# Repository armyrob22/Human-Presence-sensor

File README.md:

# Human-Presence-sensor

This is my second version of this board. My first board had many errors and was basically unusable. The pin headers were not aligned once i got the boards. This made it impossible to use the esp32 dev board I had. The biggest failure was the fact that i misplaced the USB type C connector. It was not close enough to the edge for me to plug in a power cable. This design puts the ESP32 on the PCB and lets just the mmWave 24Ghz radar board plug into a pin header. This design forced me to learn how to really design a buck converter circuit so i can take the 5V USB input power and drop it down to 3.3V required for the MCU. I took it a step further and I really drilled down on learning the physic's and the equations to derive what you need for a buck converter.

This is the result of my python script running a simulation of my chosen buck converter. I ran several different versions to see if my inductor sizing was correct. The reference design I used for most of my layout turned out to be really good for my given circuit. This is why i chose a 4.7uH inductor for my design. Even though this is my project and my own board I tried to treat it with the same care I will bring to the work place when I get to design other boards. The next big piece of the buck converter was to figure out the feedback sense resistor values required. My converter has a reference voltage of 0.8v. This means the formula I used is
Vout = Vref × (1 + R1/R2)
Vref = 0.8V, R2 = 12.7k, R1 = 40.2k
Vout = 0.8 × (1 + 40.2/12.7) = 3.33V

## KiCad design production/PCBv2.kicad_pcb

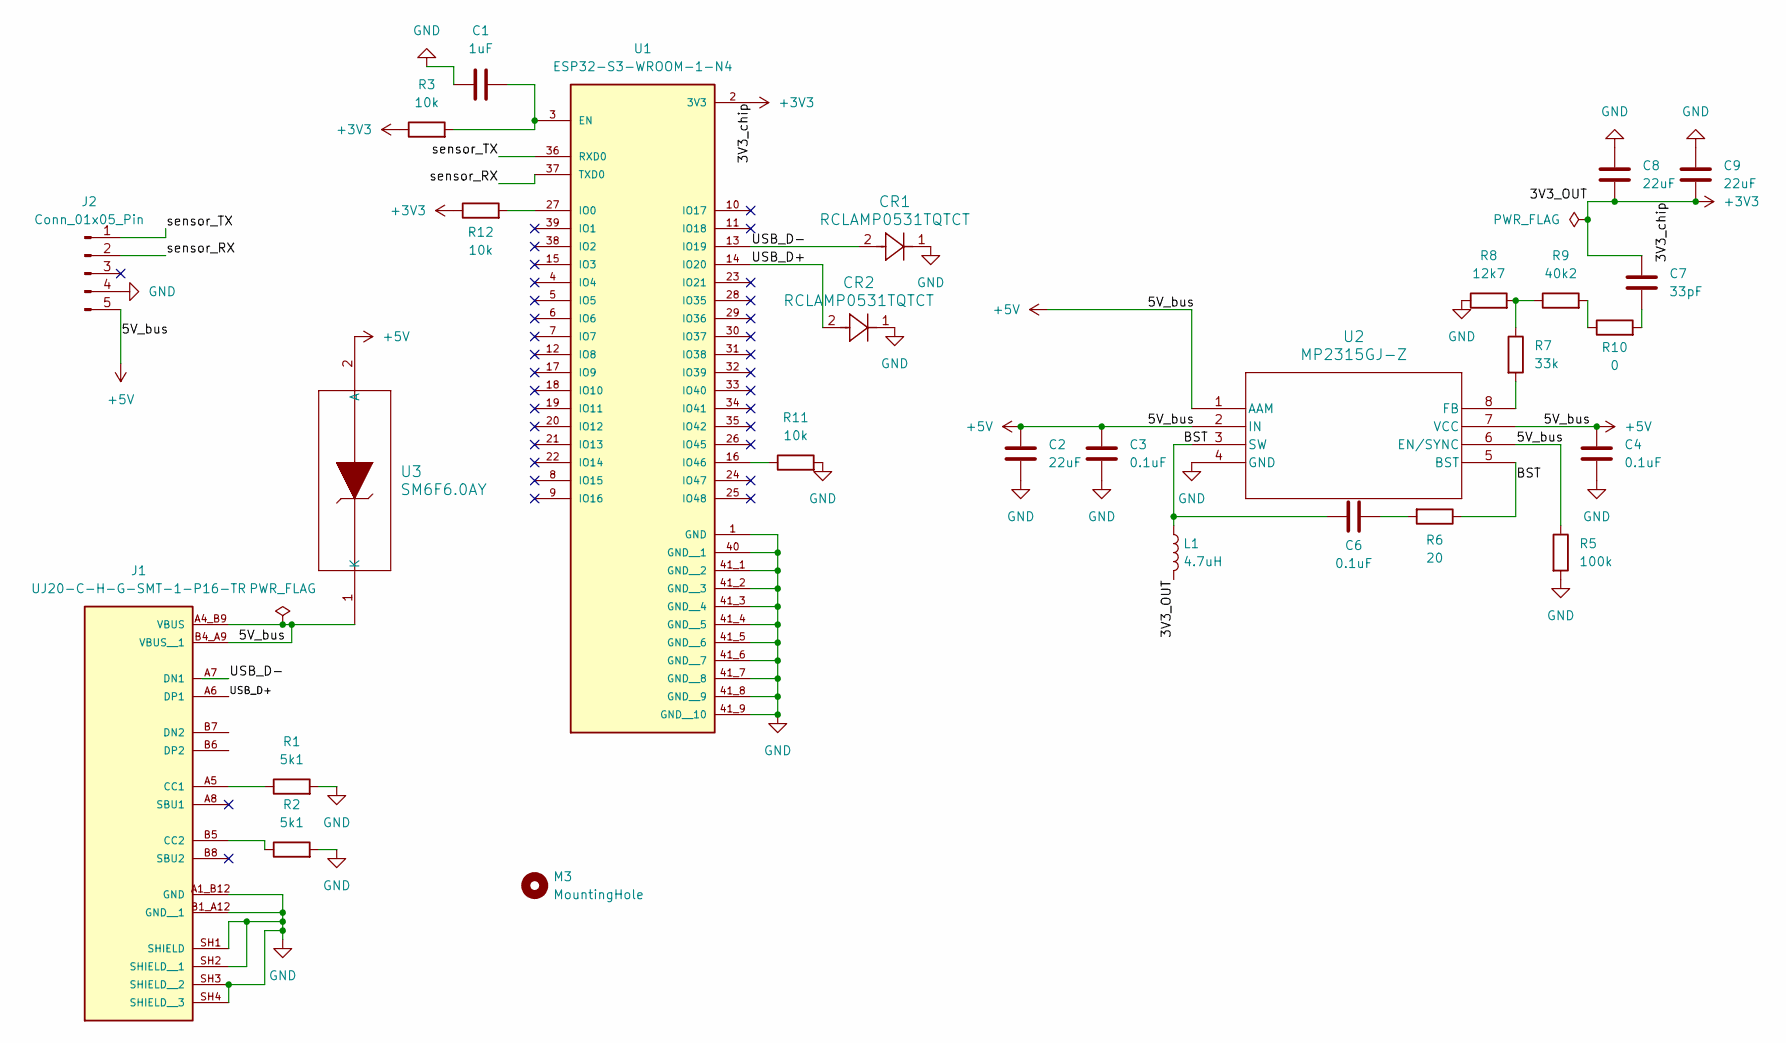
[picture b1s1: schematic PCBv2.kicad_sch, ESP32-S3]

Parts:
C1: 1uF; C_0805_2012Metric_Pad1.18x1.45mm_HandSolder
C2, C8, C9: 22uF; C_0805_2012Metric_Pad1.18x1.45mm_HandSolder
C3, C4, C6: 0.1uF; C_0805_2012Metric_Pad1.18x1.45mm_HandSolder
C7: 33pF; C_0805_2012Metric_Pad1.18x1.45mm_HandSolder
CR1, CR2: RCLAMP0531TQTCT; CR_RCLAMP053_1XP6_SEM-L
J1: UJ20-C-H-G-SMT-1-P16-TR; SAMESKY_UJ20-C-H-G-SMT-1-P16-TR; PARTREV 1.0
J2: Conn_01x05_Pin; PinHeader_1x05_P2.54mm_Vertical
L1: 4.7uH; IND_DFE322520FD-4R7M=P2_MUR
M3: MountingHole; MountingHole_3.2mm_M3_DIN965_Pad
R1, R2: 5k1; R_0805_2012Metric_Pad1.20x1.40mm_HandSolder
R3, R11, R12: 10k; R_0805_2012Metric_Pad1.20x1.40mm_HandSolder
R5: 100k; R_0805_2012Metric_Pad1.20x1.40mm_HandSolder
R6: 20; R_0805_2012Metric_Pad1.20x1.40mm_HandSolder
R7: 33k; R_0805_2012Metric_Pad1.20x1.40mm_HandSolder
R8: 12k7; R_0805_2012Metric_Pad1.20x1.40mm_HandSolder
R9: 40k2; R_0805_2012Metric_Pad1.20x1.40mm_HandSolder
R10: 0; R_0805_2012Metric_Pad1.20x1.40mm_HandSolder
U1: ESP32-S3-WROOM-1-N4; XCVR_ESP32-S3-WROOM-1-N4; PARTREV v1.0
U2: MP2315GJ-Z; TSOT23-8_MPS
U3: SM6F6.0AY; SOD128_STM-L

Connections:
+3V3: C7.2, C8.1, C9.1, L1.2, R3.1, R12.1, U1.2 (3V3)
+5V: C2.2, C3.2, C4.1, J1.A4_B9 (VBUS), J1.B4_A9 (VBUS__1), J2.5, R5.1, U2.1 (AAM), U2.2 (IN), U2.6 (EN/SYNC), U2.7 (VCC), U3.1 (K), U3.2 (A)
/BST: C6.1, L1.1, R6.1, U2.3 (SW), U2.5 (BST)
/USB_D+: CR2.2, J1.A6 (DP1), U1.14 (IO20)
/USB_D-: CR1.2, J1.A7 (DN1), U1.13 (IO19)
/sensor_RX: J2.2, U1.37 (TXD0)
/sensor_TX: J2.1, U1.36 (RXD0)
GND: C1.1, C2.1, C3.1, C4.2, C8.2, C9.2, CR1.1, CR2.1, J1.A1_B12 (GND), J1.B1_A12 (GND__1), J1.SH1 (SHIELD), J1.SH2 (SHIELD__1), J1.SH3 (SHIELD__2), J1.SH4 (SHIELD__3), J2.4, R1.2, R2.2, R5.2, R8.1, R11.2, U1.1 (GND), U1.40 (GND__1), U1.41_1 (GND__2), U1.41_2 (GND__3), U1.41_3 (GND__4), U1.41_4 (GND__5), U1.41_5 (GND__6), U1.41_6 (GND__7), U1.41_7 (GND__8), U1.41_8 (GND__9), U1.41_9 (GND__10), U1.41_10, U1.41_11, U1.41_12, U1.41_13, U1.41_14, U1.41_15, U1.41_16, U1.41_17, U1.41_18, U1.41_19, U1.41_20, U1.41_21, U2.4 (GND)
unnamed: C6.2, R6.2
unnamed: C7.1, R10.2
unnamed: J1.A5 (CC1), R1.1
unnamed: J1.B5 (CC2), R2.1
unnamed: R7.1, R8.2, R9.1
unnamed: R9.2, R10.1
unnamed: C1.2, R3.2, U1.3 (EN)
unnamed: R12.2, U1.27 (IO0)
unnamed: R11.1, U1.16 (IO46)
unnamed: R7.2, U2.8 (FB)

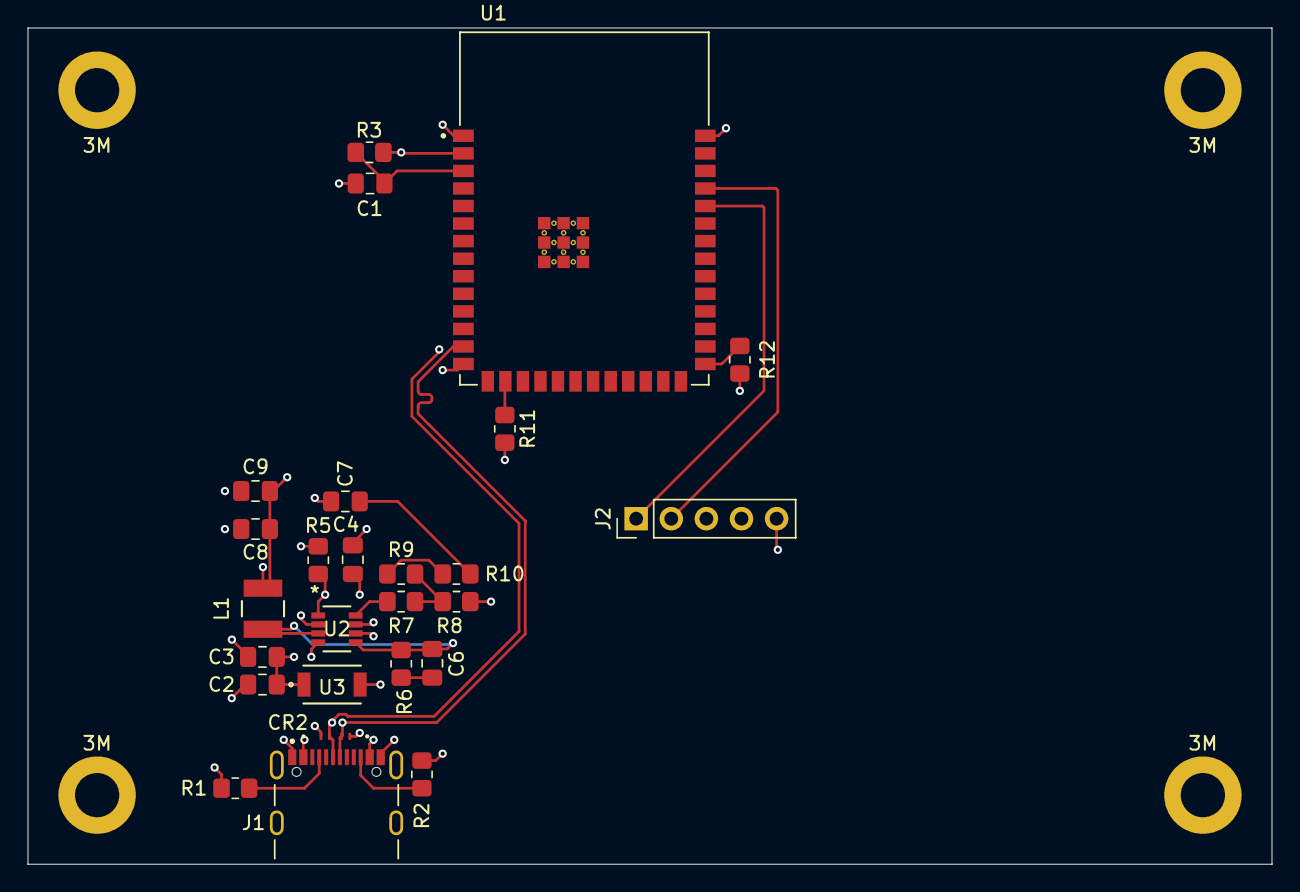
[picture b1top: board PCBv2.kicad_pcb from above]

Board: 4 copper layers, 90.0 x 60.5 mm, 31 parts (0 on the bottom side), 18 nets.

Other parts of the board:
3M, 3M#2, 3M#3, 3M#4: MountingHole_3.2mm_M3_DIN965_Pad

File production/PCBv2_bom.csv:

Designator,Footprint,Quantity,Value,LCSC Part #
C1,0805,1,1uF,
"C2, C8, C9",0805,3,22uF,
"C3, C4, C6",0805,3,0.1uF,
C7,0805,1,33pF,
"CR1, CR2",CR_RCLAMP053_1XP6_SEM-L,2,RCLAMP0531TQTCT,
J1,SAMESKY_UJ20-C-H-G-SMT-1-P16-TR,1,UJ20-C-H-G-SMT-1-P16-TR,
J2,PinHeader_1x05_P2.54mm_Vertical,1,Conn_01x05_Pin,
L1,IND_DFE322520FD-4R7M=P2_MUR,1,4.7uH,
"R1, R2",0805,2,5k1,
R10,0805,1,0,
"R11, R12, R3",0805,3,10k,
R5,0805,1,100k,
R6,0805,1,20,
R7,0805,1,33k,
R8,0805,1,12k7,
R9,0805,1,40k2,
U1,XCVR_ESP32-S3-WROOM-1-N4,1,ESP32-S3-WROOM-1-N4,
U2,TSOT23-8_MPS,1,MP2315GJ-Z,
U3,SOD128_STM-L,1,SM6F6.0AY,
